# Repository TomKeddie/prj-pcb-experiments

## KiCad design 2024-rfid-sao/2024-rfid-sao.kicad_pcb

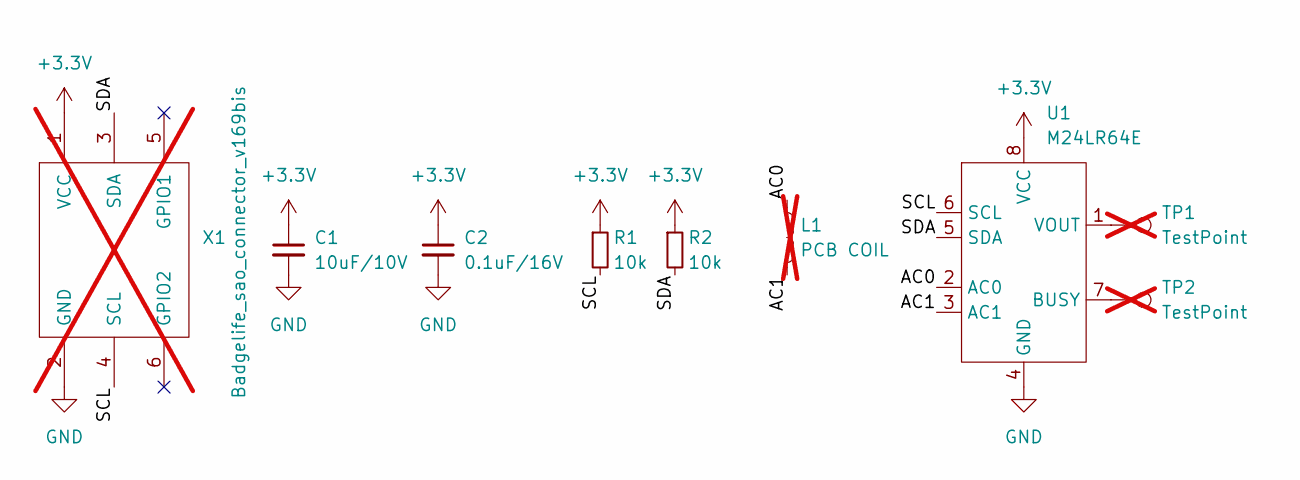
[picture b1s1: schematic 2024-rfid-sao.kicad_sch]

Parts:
C1: 10uF/10V; C_0603_1608Metric; LCSC C19702
C2: 0.1uF/16V; C_0402_1005Metric; LCSC C1525
L1: PCB COIL; nrf_r20; not fitted
R1, R2: 10k; R_0402_1005Metric; LCSC C25744
TP1, TP2: TestPoint; TestPoint_Pad_D2.0mm; not fitted
U1: M24LR64E; SOIC-8_3.9x4.9mm_P1.27mm; LCSC C157372
X1: Badgelife_sao_connector_v169bis; PinHeader_2x03_P2.54mm_Vertical; not fitted

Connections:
+3.3V: C1.1, C2.1, R1.1, R2.1, U1.8 (VCC), X1.1 (VCC)
/AC0: L1.1, U1.2 (AC0)
/AC1: L1.2, U1.3 (AC1)
/SCL: R1.2, U1.6 (SCL), X1.4 (SCL)
/SDA: R2.2, U1.5 (SDA), X1.3 (SDA)
GND: C1.2, C2.2, U1.4 (GND), X1.2 (GND)
unnamed: TP2.1, U1.7 (BUSY)
unnamed: TP1.1, U1.1 (VOUT)

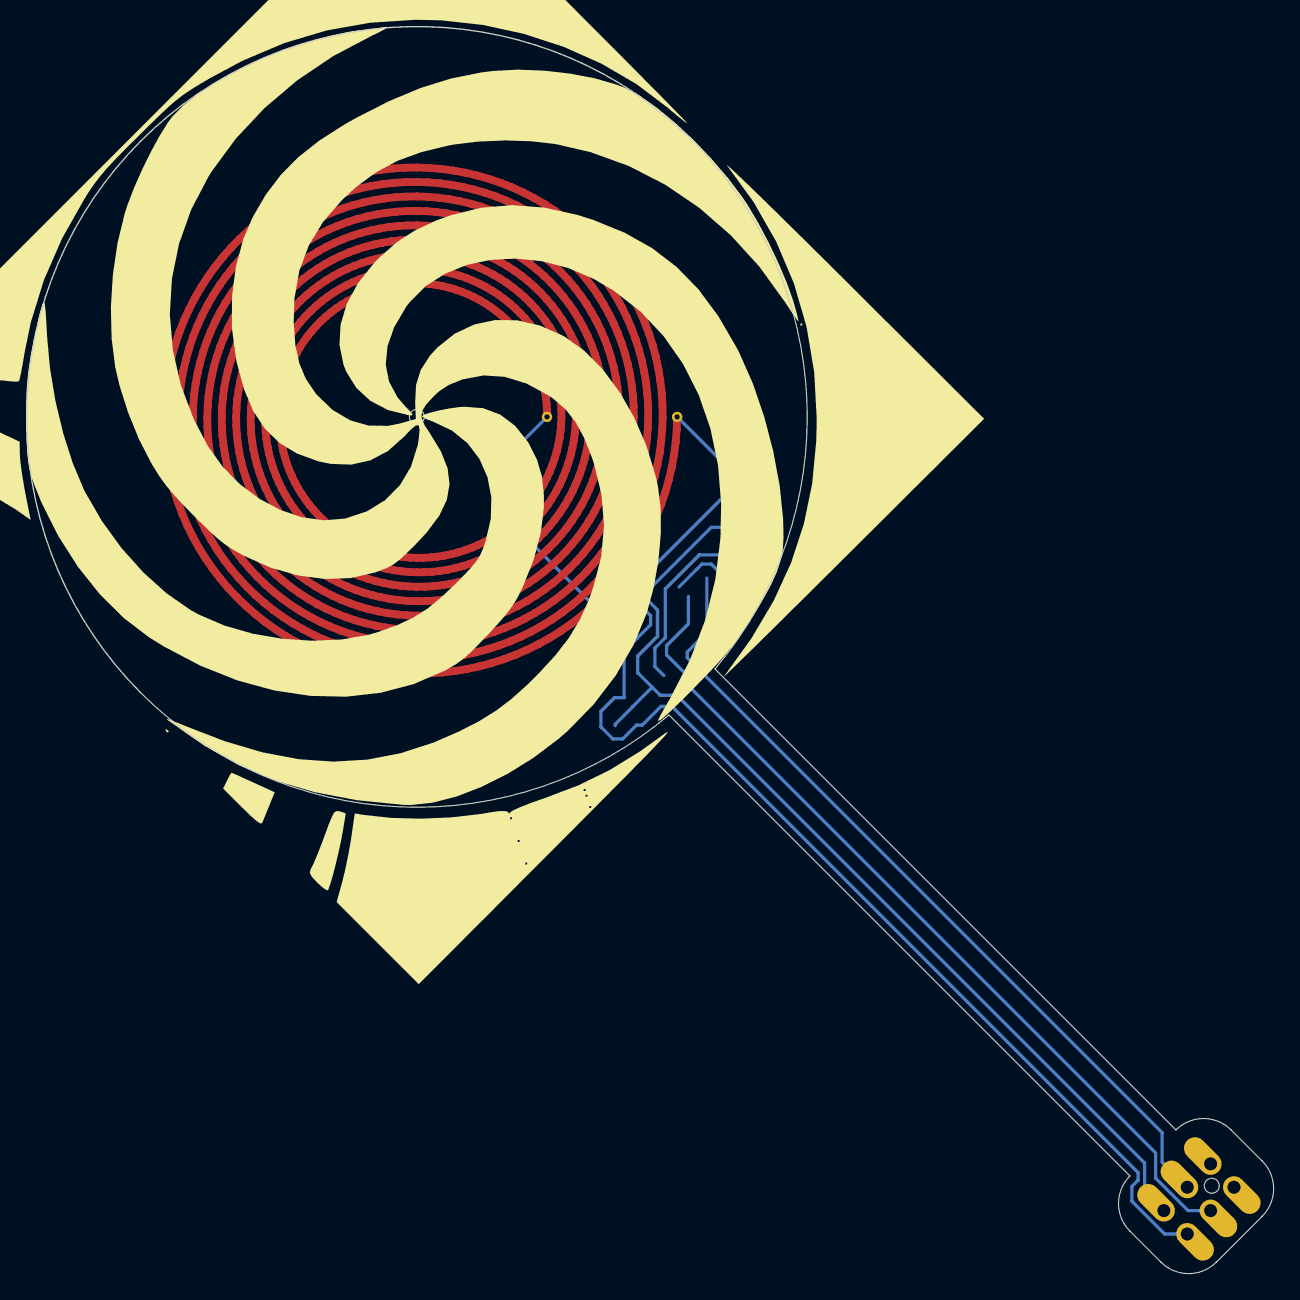
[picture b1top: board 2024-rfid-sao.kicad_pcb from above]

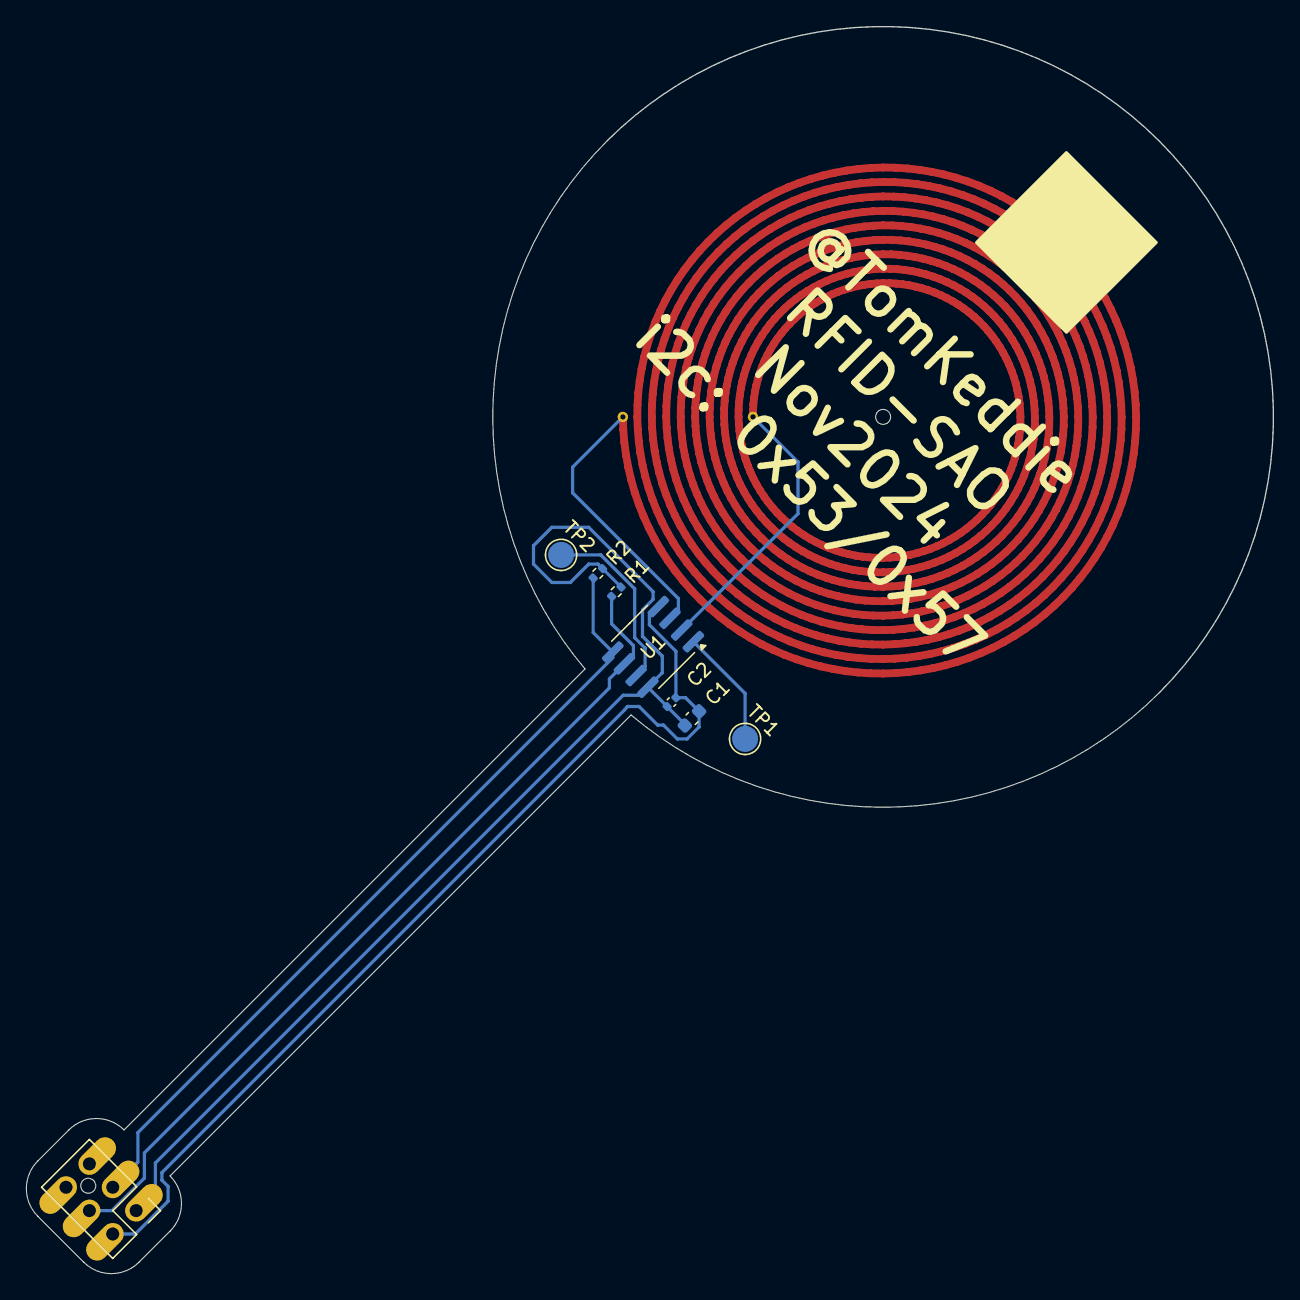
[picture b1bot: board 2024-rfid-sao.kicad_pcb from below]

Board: 2 copper layers, 95.8 x 95.8 mm, 9 parts (8 on the bottom side), 8 nets.

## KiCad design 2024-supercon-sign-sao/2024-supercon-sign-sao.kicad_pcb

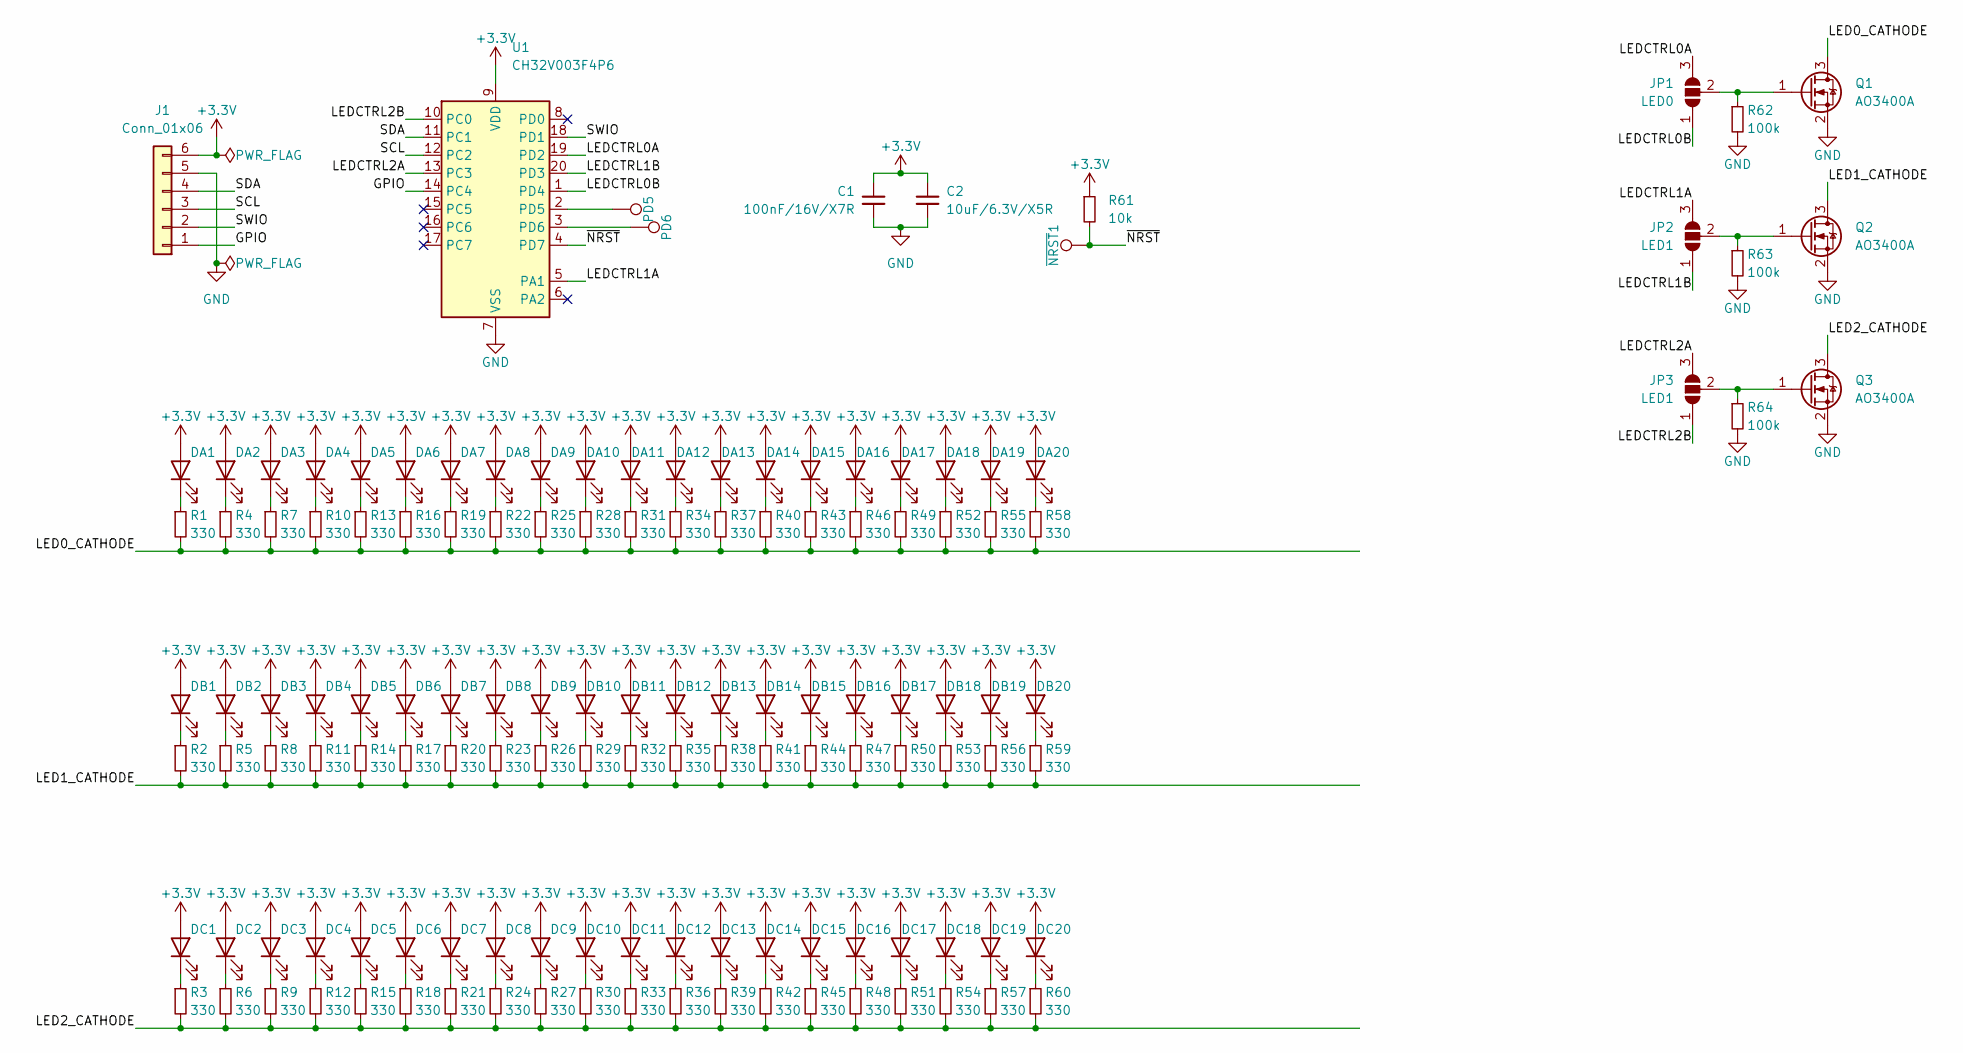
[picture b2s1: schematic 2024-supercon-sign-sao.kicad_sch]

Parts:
C1: 100nF/16V/X7R; C_0402_1005Metric; MFGPN CL05B104KO5NNNC; LCSC C1525
C2: 10uF/6.3V/X5R; C_0402_1005Metric; MFGPN CL05A106MQ5NUNC; LCSC C15525
DA1, DA2, DA3, DA4, DA5, DA6, DA7, DA8, DA9, DA10, DA11, DA12, DA13, DA14, DA15, DA16, DA17, DA18, DA19, DA20: LED_AMBER; LED_0603_1608Metric; LCSC C2286
DB1, DB2, DB3, DB4, DB5, DB6, DB7, DB8, DB9, DB10, DB11, DB12, DB13, DB14, DB15, DB16, DB17, DB18, DB19, DB20: LED_AMBER; LED_0603_1608Metric; LCSC C2286
DC1, DC2, DC3, DC4, DC5, DC6, DC7, DC8, DC9, DC10, DC11, DC12, DC13, DC14, DC15, DC16, DC17, DC18, DC19, DC20: LED_AMBER; LED_0603_1608Metric; LCSC C2286
J1: Conn_01x06; PinHeader_2x03_P2.54mm_Vertical
JP1: LED0; SolderJumper-3_P1.3mm_Open_RoundedPad1.0x1.5mm
JP2, JP3: LED1; SolderJumper-3_P1.3mm_Open_RoundedPad1.0x1.5mm
PD5, PD6: TestPoint; TestPoint_Pad_D2.0mm
Q1, Q2, Q3: AO3400A; SOT-23-GSD; LCSC C20917
R1, R2, R3, R4, R5, R6, R7, R8, R9, R10, R11, R12, R13, R14, R15, R16, R17, R18, R19, R20, R21, R22, R23, R24, R25, R26, R27, R28, R29, R30, R31, R32, R33, R34, R35, R36, R37, R38, R39, R40, R41, R42, R43, R44, R45, R46, R47, R48, R49, R50, R51, R52, R53, R54, R55, R56, R57, R58, R59, R60: 330; R_0402_1005Metric; MFGPN 0402WGF3300TCE; LCSC C25104
R61: 10k; R_0402_1005Metric; MFGPN 0402WGF1002TCE; LCSC C25744
R62, R63, R64: 100k; R_0402_1005Metric; MFGPN 0402WGF1003TCE; LCSC C25741
U1: CH32V003F4P6; TSSOP-20_4.4x6.5mm_P0.65mm; LCSC C5187096
~{NRST}1: ~{NRST}; TestPoint_Pad_D2.0mm

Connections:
+3.3V: C1.1, C2.1, DA1.2 (A), DA2.2 (A), DA3.2 (A), DA4.2 (A), DA5.2 (A), DA6.2 (A), DA7.2 (A), DA8.2 (A), DA9.2 (A), DA10.2 (A), DA11.2 (A), DA12.2 (A), DA13.2 (A), DA14.2 (A), DA15.2 (A), DA16.2 (A), DA17.2 (A), DA18.2 (A), DA19.2 (A), DA20.2 (A), DB1.2 (A), DB2.2 (A), DB3.2 (A), DB4.2 (A), DB5.2 (A), DB6.2 (A), DB7.2 (A), DB8.2 (A), DB9.2 (A), DB10.2 (A), DB11.2 (A), DB12.2 (A), DB13.2 (A), DB14.2 (A), DB15.2 (A), DB16.2 (A), DB17.2 (A), DB18.2 (A), DB19.2 (A), DB20.2 (A), DC1.2 (A), DC2.2 (A), DC3.2 (A), DC4.2 (A), DC5.2 (A), DC6.2 (A), DC7.2 (A), DC8.2 (A), DC9.2 (A), DC10.2 (A), DC11.2 (A), DC12.2 (A), DC13.2 (A), DC14.2 (A), DC15.2 (A), DC16.2 (A), DC17.2 (A), DC18.2 (A), DC19.2 (A), DC20.2 (A), J1.6, R61.1, U1.9 (VDD)
/GPIO: J1.1, U1.14 (PC4)
/LED0_CATHODE: Q1.3 (D), R1.2, R4.2, R7.2, R10.2, R13.2, R16.2, R19.2, R22.2, R25.2, R28.2, R31.2, R34.2, R37.2, R40.2, R43.2, R46.2, R49.2, R52.2, R55.2, R58.2
/LED1_CATHODE: Q2.3 (D), R2.2, R5.2, R8.2, R11.2, R14.2, R17.2, R20.2, R23.2, R26.2, R29.2, R32.2, R35.2, R38.2, R41.2, R44.2, R47.2, R50.2, R53.2, R56.2, R59.2
/LED2_CATHODE: Q3.3 (D), R3.2, R6.2, R9.2, R12.2, R15.2, R18.2, R21.2, R24.2, R27.2, R30.2, R33.2, R36.2, R39.2, R42.2, R45.2, R48.2, R51.2, R54.2, R57.2, R60.2
/LEDCTRL0A: JP1.3 (B), U1.19 (PD2)
/LEDCTRL0B: JP1.1 (A), U1.1 (PD4)
/LEDCTRL1A: JP2.3 (B), U1.5 (PA1)
/LEDCTRL1B: JP2.1 (A), U1.20 (PD3)
/LEDCTRL2A: JP3.3 (B), U1.13 (PC3)
/LEDCTRL2B: JP3.1 (A), U1.10 (PC0)
/SCL: J1.3, U1.12 (PC2)
/SDA: J1.4, U1.11 (PC1)
/SWIO: J1.2, U1.18 (PD1)
/~NRST: R61.2, U1.4 (PD7), ~{NRST}1.1
GND: C1.2, C2.2, J1.5, Q1.2 (S), Q2.2 (S), Q3.2 (S), R62.2, R63.2, R64.2, U1.7 (VSS)
unnamed: DA1.1 (K), R1.1
unnamed: DA2.1 (K), R4.1
unnamed: DA3.1 (K), R7.1
unnamed: DA4.1 (K), R10.1
unnamed: DA5.1 (K), R13.1
unnamed: DA6.1 (K), R16.1
unnamed: DA7.1 (K), R19.1
unnamed: DA8.1 (K), R22.1
unnamed: DA9.1 (K), R25.1
unnamed: DA10.1 (K), R28.1
unnamed: DA11.1 (K), R31.1
unnamed: DA12.1 (K), R34.1
unnamed: DA13.1 (K), R37.1
unnamed: DA14.1 (K), R40.1
unnamed: DA15.1 (K), R43.1
unnamed: DA16.1 (K), R46.1
unnamed: DA17.1 (K), R49.1
unnamed: DA18.1 (K), R52.1
unnamed: DA19.1 (K), R55.1
unnamed: DA20.1 (K), R58.1
unnamed: DB1.1 (K), R2.1
unnamed: DB2.1 (K), R5.1
unnamed: DB3.1 (K), R8.1
unnamed: DB4.1 (K), R11.1
unnamed: DB5.1 (K), R14.1
unnamed: DB6.1 (K), R17.1
unnamed: DB7.1 (K), R20.1
unnamed: DB8.1 (K), R23.1
unnamed: DB9.1 (K), R26.1
unnamed: DB10.1 (K), R29.1
unnamed: DB11.1 (K), R32.1
unnamed: DB12.1 (K), R35.1
unnamed: DB13.1 (K), R38.1
unnamed: DB14.1 (K), R41.1
unnamed: DB15.1 (K), R44.1
unnamed: DB16.1 (K), R47.1
unnamed: DB17.1 (K), R50.1
unnamed: DB18.1 (K), R53.1
unnamed: DB19.1 (K), R56.1
unnamed: DB20.1 (K), R59.1
unnamed: DC1.1 (K), R3.1
unnamed: DC2.1 (K), R6.1
unnamed: DC3.1 (K), R9.1
unnamed: DC4.1 (K), R12.1
unnamed: DC5.1 (K), R15.1
unnamed: DC6.1 (K), R18.1
unnamed: DC7.1 (K), R21.1
unnamed: DC8.1 (K), R24.1
unnamed: DC9.1 (K), R27.1
unnamed: DC10.1 (K), R30.1
unnamed: DC11.1 (K), R33.1
unnamed: DC12.1 (K), R36.1
unnamed: DC13.1 (K), R39.1
unnamed: DC14.1 (K), R42.1
unnamed: DC15.1 (K), R45.1
unnamed: DC16.1 (K), R48.1
unnamed: DC17.1 (K), R51.1
unnamed: DC18.1 (K), R54.1
unnamed: DC19.1 (K), R57.1
unnamed: DC20.1 (K), R60.1
unnamed: JP1.2 (C), Q1.1 (G), R62.1
unnamed: JP2.2 (C), Q2.1 (G), R63.1
unnamed: JP3.2 (C), Q3.1 (G), R64.1
unnamed: PD5.1, U1.2 (PD5)
unnamed: PD6.1, U1.3 (PD6)

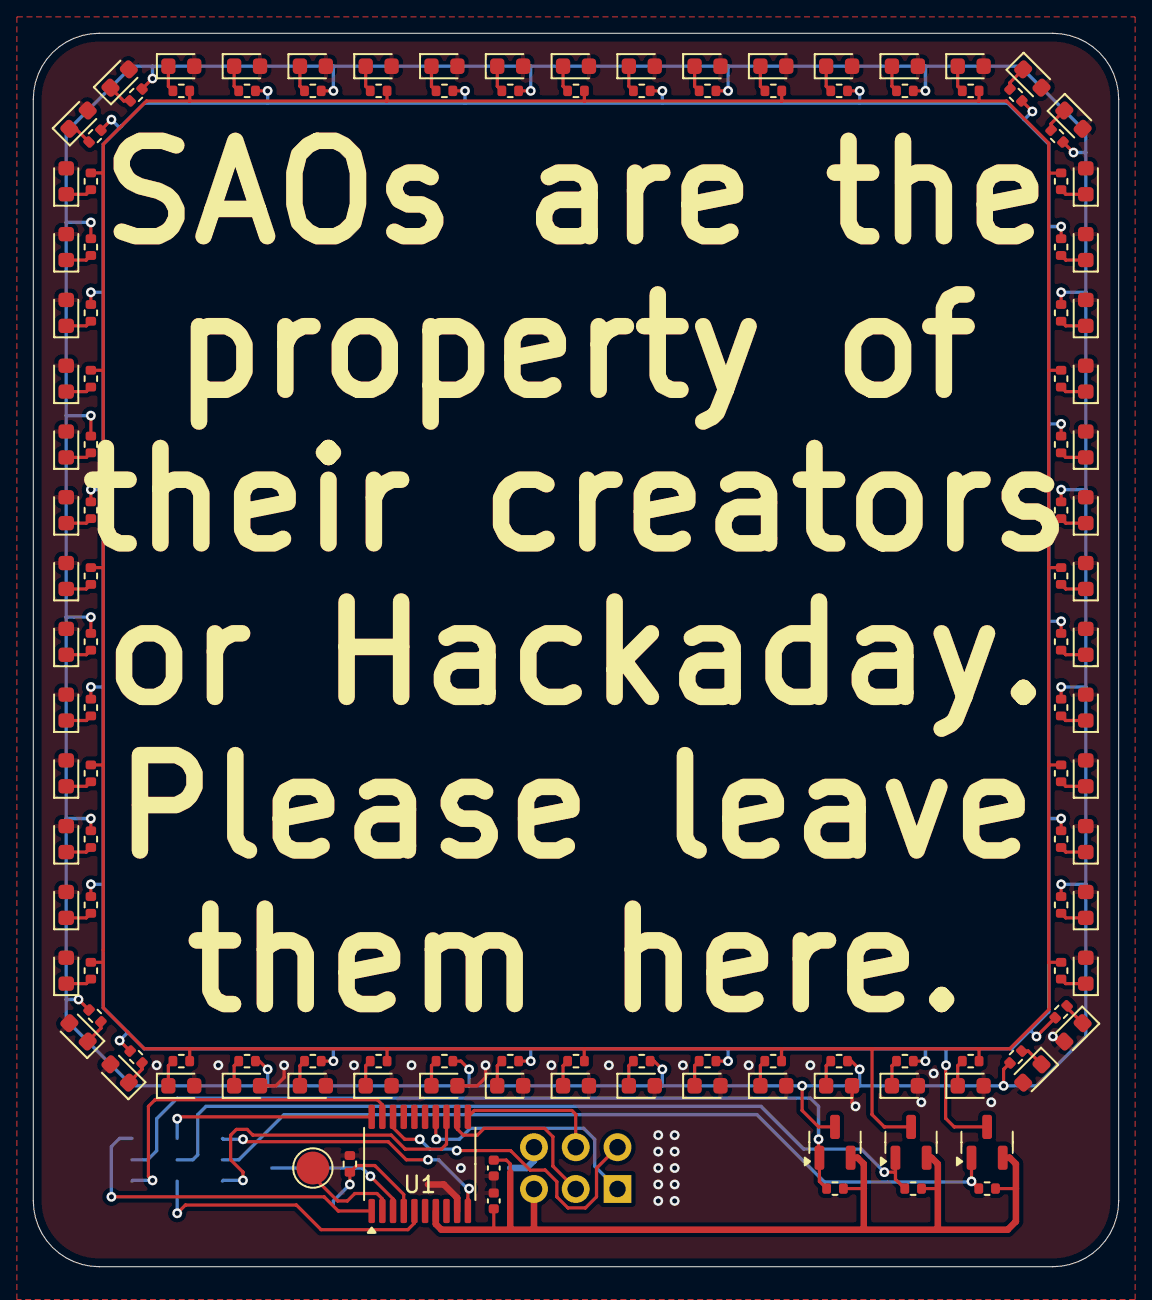
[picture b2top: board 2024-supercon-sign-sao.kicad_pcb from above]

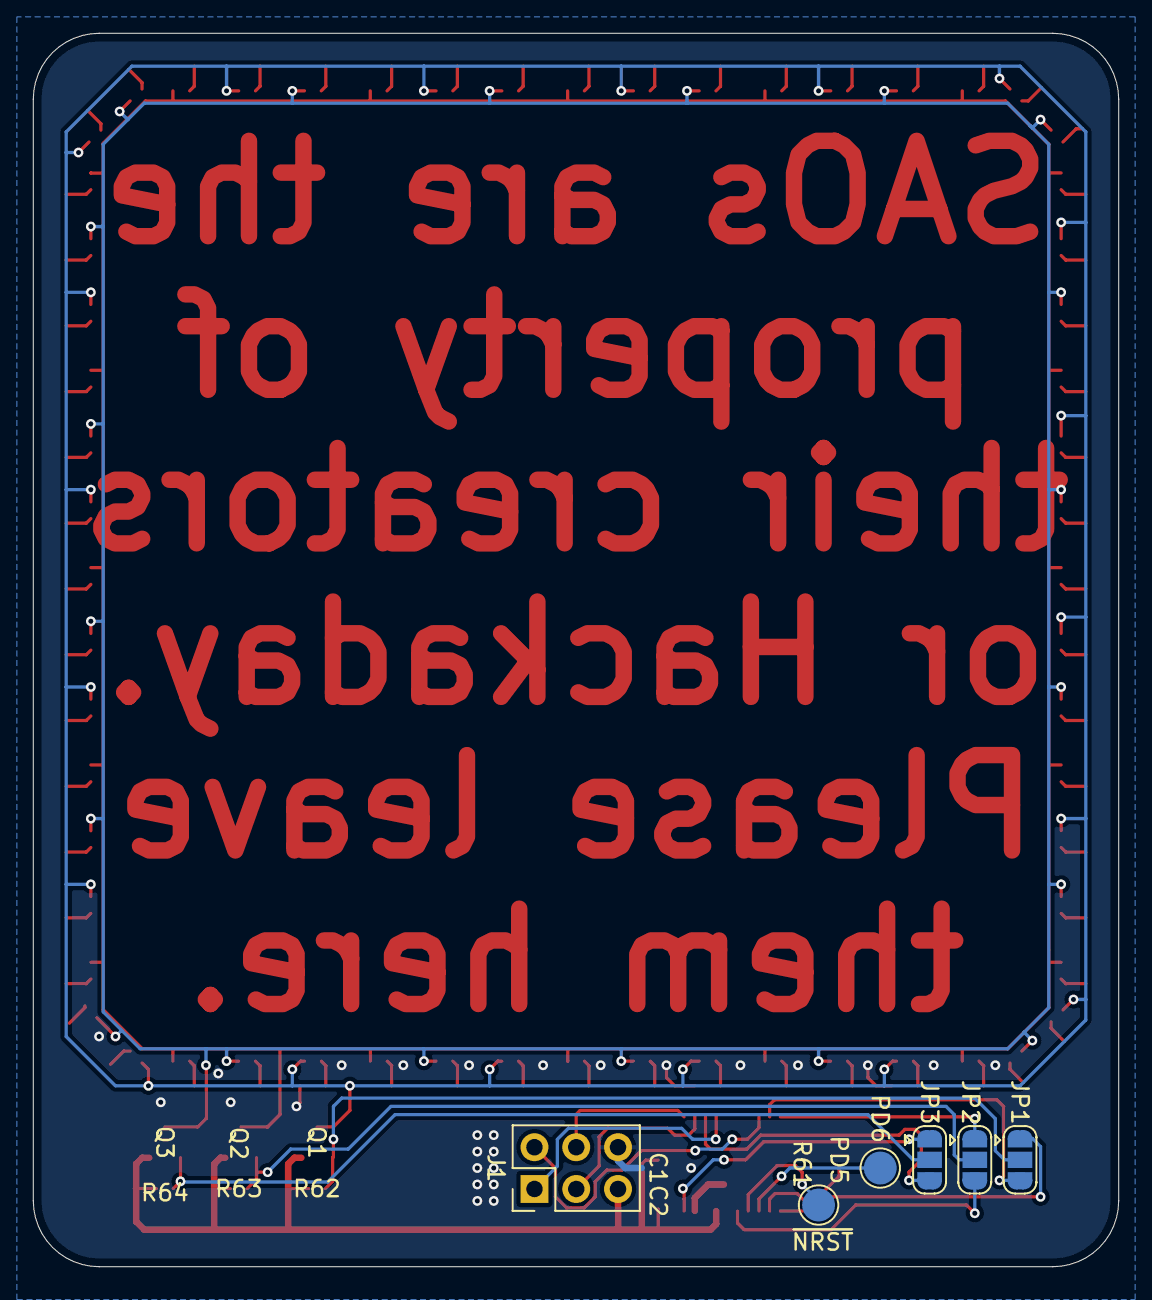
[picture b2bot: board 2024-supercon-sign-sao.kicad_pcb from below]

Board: 2 copper layers, 66.0 x 75.0 mm, 136 parts (5 on the bottom side), 81 nets.

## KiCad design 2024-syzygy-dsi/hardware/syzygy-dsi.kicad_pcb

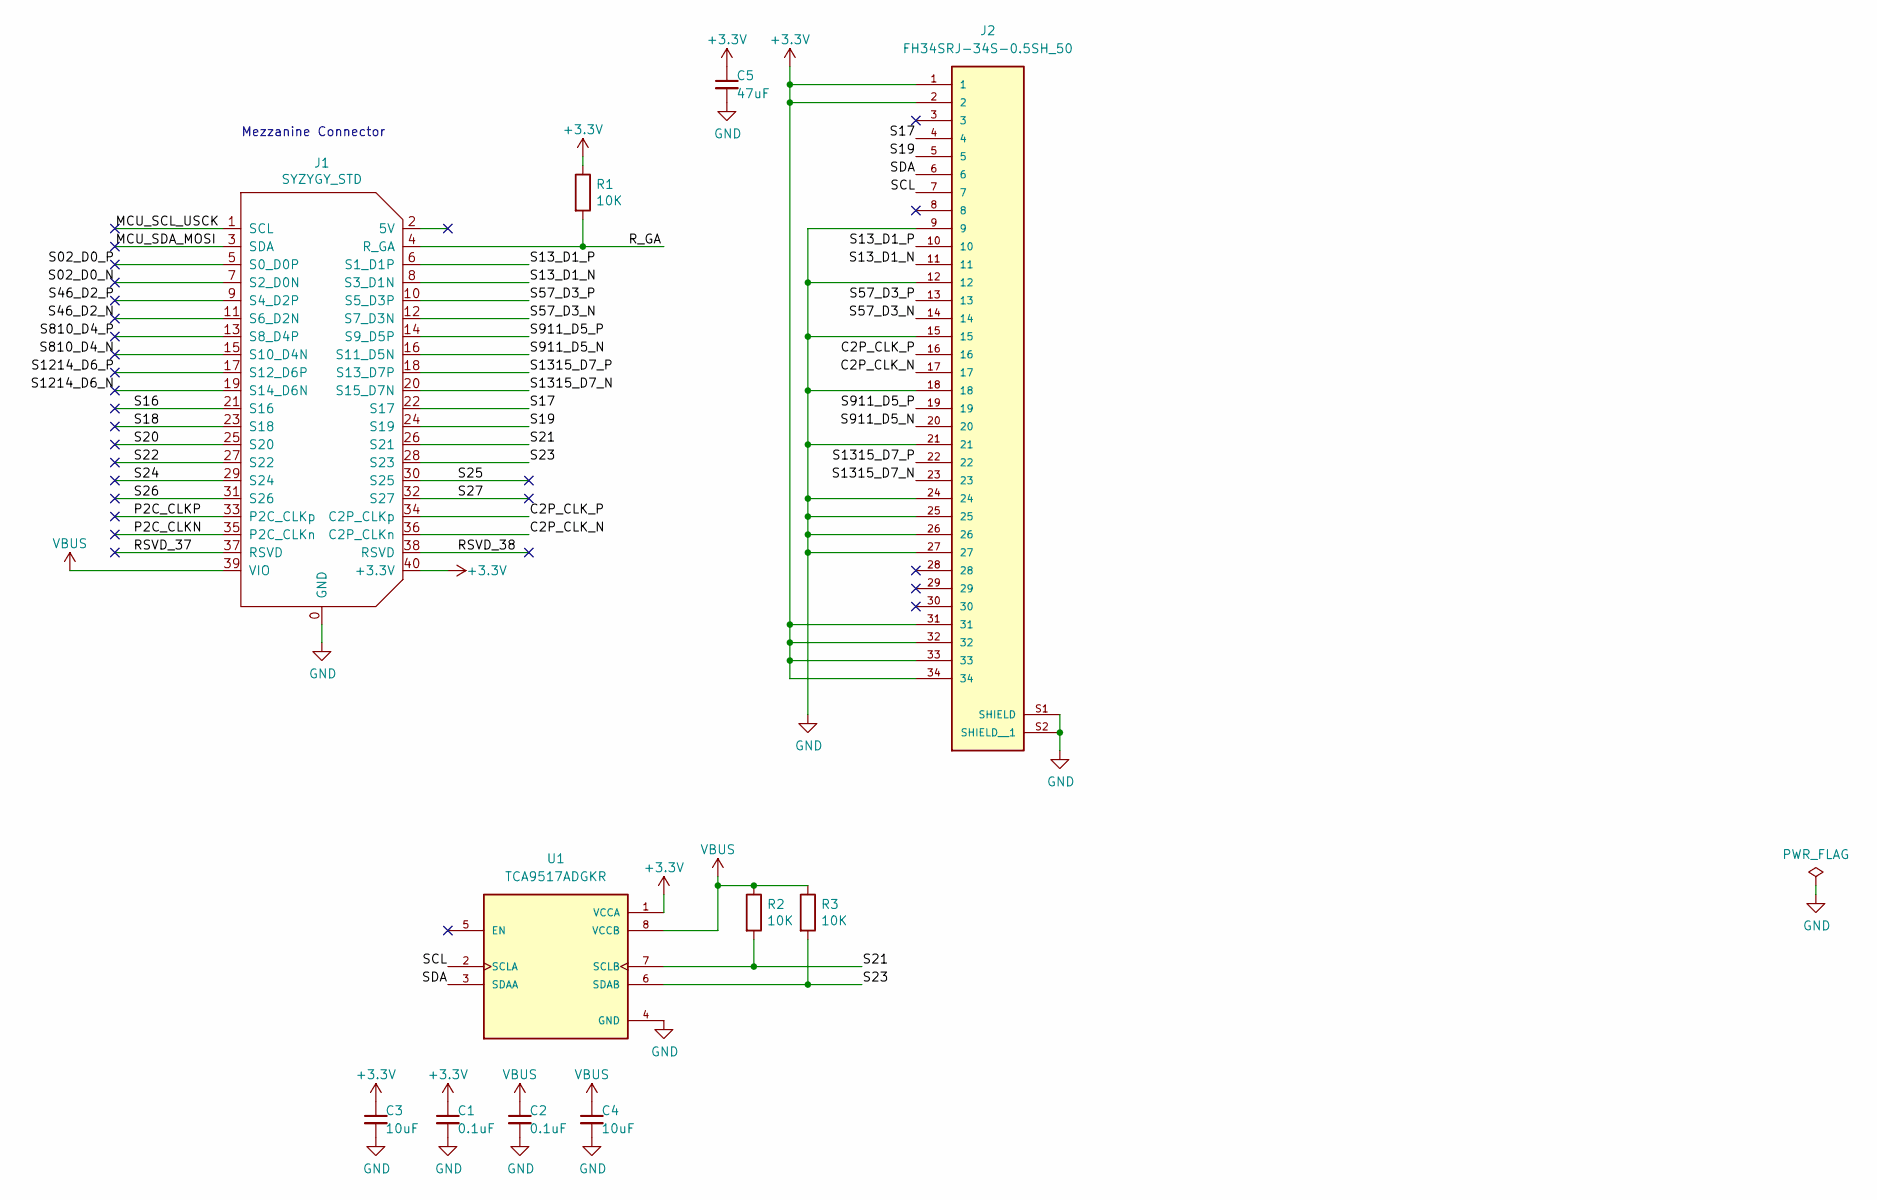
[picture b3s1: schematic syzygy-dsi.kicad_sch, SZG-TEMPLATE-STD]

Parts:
C1, C2: 0.1uF; C_0603_1608Metric
C3, C4: 10uF; C_0603_1608Metric
C5: 47uF; C_0805_2012Metric
J1: SYZYGY_STD; QTE-020-01-F-D-A; Manufacturer_PN QTE-020-01-F-D-A
J2: FH34SRJ-34S-0.5SH_50; HRS_FH34SRJ-34S-0.5SH_50_
R1, R2, R3: 10K; R_0603_1608Metric
U1: TCA9517ADGKR; IC_TCA9517ADGKR; PARTREV C

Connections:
+3.3V: C1.1, C3.1, C5.1, J1.40 (+3.3V), J2.1, J2.2, J2.31, J2.32, J2.33, J2.34, R1.1, U1.1 (VCCA)
/C2P_CLK_N: J1.36 (C2P_CLKn), J2.17
/C2P_CLK_P: J1.34 (C2P_CLKp), J2.16
/MCU_SCL_USCK: J1.1 (SCL)
/MCU_SDA_MOSI: J1.3 (SDA)
/P2C_CLKN: J1.35 (P2C_CLKn)
/P2C_CLKP: J1.33 (P2C_CLKp)
/RSVD_37: J1.37 (RSVD)
/RSVD_38: J1.38 (RSVD)
/R_GA: J1.4 (R_GA), R1.2
/S02_D0_N: J1.7 (S2_D0N)
/S02_D0_P: J1.5 (S0_D0P)
/S13_D1_N: J1.8 (S3_D1N), J2.11
/S13_D1_P: J1.6 (S1_D1P), J2.10
/S16: J1.21 (S16)
/S17: J1.22 (S17), J2.4
/S18: J1.23 (S18)
/S19: J1.24 (S19), J2.5
/S20: J1.25 (S20)
/S21: J1.26 (S21), R2.2, U1.7 (SCLB)
/S22: J1.27 (S22)
/S23: J1.28 (S23), R3.2, U1.6 (SDAB)
/S24: J1.29 (S24)
/S25: J1.30 (S25)
/S26: J1.31 (S26)
/S27: J1.32 (S27)
/S46_D2_N: J1.11 (S6_D2N)
/S46_D2_P: J1.9 (S4_D2P)
/S57_D3_N: J1.12 (S7_D3N), J2.14
/S57_D3_P: J1.10 (S5_D3P), J2.13
/S810_D4_N: J1.15 (S10_D4N)
/S810_D4_P: J1.13 (S8_D4P)
/S911_D5_N: J1.16 (S11_D5N), J2.20
/S911_D5_P: J1.14 (S9_D5P), J2.19
/S1214_D6_N: J1.19 (S14_D6N)
/S1214_D6_P: J1.17 (S12_D6P)
/S1315_D7_N: J1.20 (S15_D7N), J2.23
/S1315_D7_P: J1.18 (S13_D7P), J2.22
/SCL: J2.7, U1.2 (SCLA)
/SDA: J2.6, U1.3 (SDAA)
GND: C1.2, C2.2, C3.2, C4.2, C5.2, J1.0 (GND), J2.9, J2.12, J2.15, J2.18, J2.21, J2.24, J2.25, J2.26, J2.27, J2.S1 (SHIELD), J2.S2 (SHIELD__1), U1.4 (GND)
VBUS: C2.1, C4.1, J1.39 (VIO), R2.1, R3.1, U1.8 (VCCB)

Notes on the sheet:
Mezzanine Connector

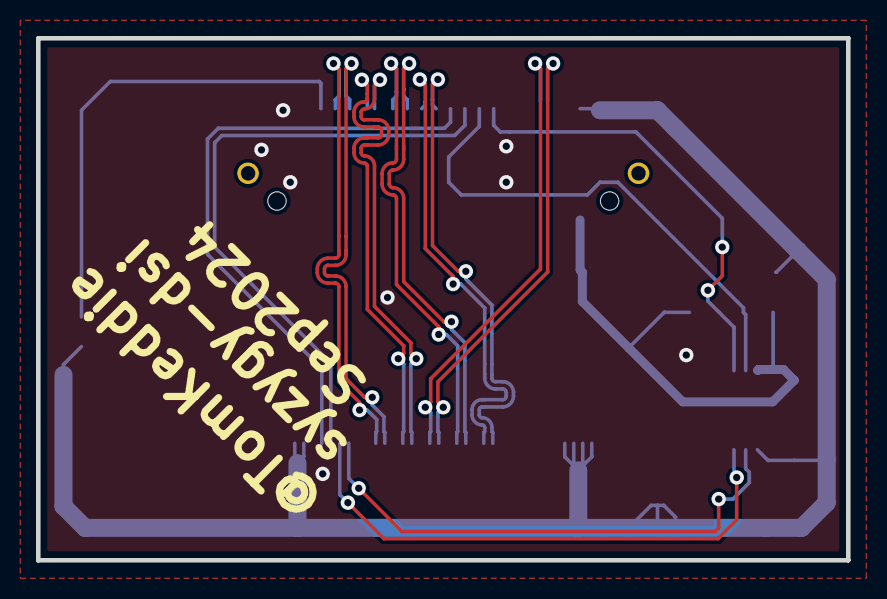
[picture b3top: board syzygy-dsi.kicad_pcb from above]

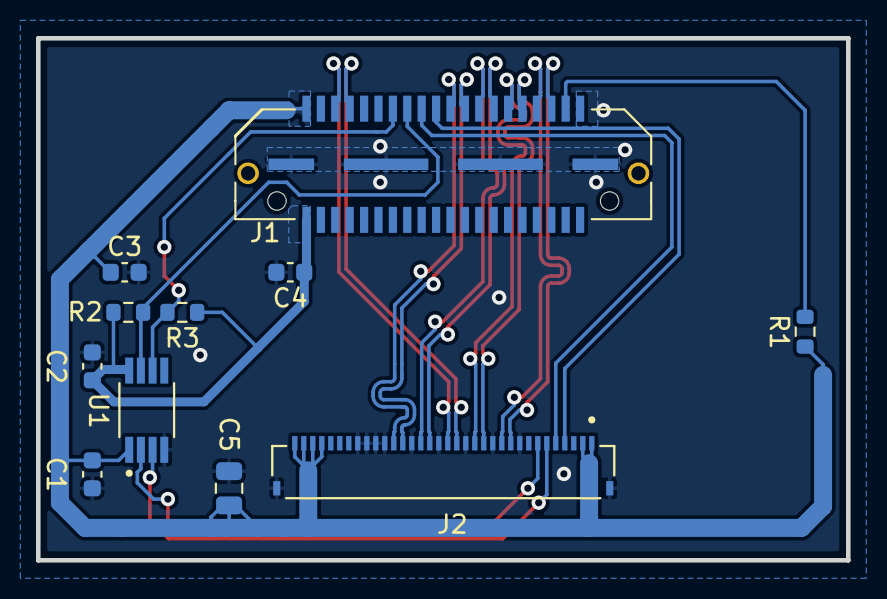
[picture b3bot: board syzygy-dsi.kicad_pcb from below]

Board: 4 copper layers, 45.0 x 29.0 mm, 11 parts (11 on the bottom side), 20 nets.
